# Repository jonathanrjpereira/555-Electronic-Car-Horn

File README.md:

# Electronic Horn | Car / Bike / Bicycle | 555 386 |
The LM555 generates an electronic horn signal which is amplified by an LM386.
The horn can be used on a car, scooter, cycle and motorbike.

**Full Video:**

**Order PCB:**  [PCBWay](https://bit.ly/2VrASCW)

## Electronic Components
| Qty | Component | Buy |
| ------------- | ------------- | ------------- |
| 1 | IC 555 |[AliExpress](http://s.click.aliexpress.com/e/sCv1ACC) |
| 1 | IC LM386 |[AliExpress](http://s.click.aliexpress.com/e/c1pixqXe) |
| 2 | IC Holder |[AliExpress](http://s.click.aliexpress.com/e/cHvnfsrA) |
| 1 | 10Ω 1KΩ 2KΩ Resistor |[AliExpress](http://s.click.aliexpress.com/e/bh4eqrQs) |
| 3 | 10KΩ Potentiometer |[AliExpress](http://s.click.aliexpress.com/e/bN0jkp8y) |
| 1 | Tactile Momentary Push Buttons |[AliExpress](http://s.click.aliexpress.com/e/c77Ajrpq) |
| 1 | 5mm LED |[AliExpress](http://s.click.aliexpress.com/e/wuFpLXS) |
| 1 | 0.1uF 10uF 100uF 220uF Capacitor |[AliExpress](http://s.click.aliexpress.com/e/c9FHzl5W) |
| 1 | 10nF 47nF 0.1uF Capacitor |[AliExpress](http://s.click.aliexpress.com/e/SX7eHuG) |
| 1 | Speaker |[AliExpress](http://s.click.aliexpress.com/e/brMJh46c) |
| 1 | 9V Battery Holder |[AliExpress](http://s.click.aliexpress.com/e/c3jbp72Y) |
| 1 | 9V Battery |[AliExpress](http://s.click.aliexpress.com/e/bbDirGHE) |
| 1 | PCB |[AliExpress](http://s.click.aliexpress.com/e/dhgwzKY) |

| Tools | Buy |
|--|--|
|Soldering Iron|[AliExpress](http://s.click.aliexpress.com/e/E83bSJI) |
|Soldering Wire|[AliExpress](http://s.click.aliexpress.com/e/PdhB0nm) |
|Mini PCB Hand Drill + Bits|[AliExpress](http://s.click.aliexpress.com/e/b93tomjI) |
|Wire Cutter|[AliExpress](http://s.click.aliexpress.com/e/bHFL9vLi) |
|Wire Stripper|[AliExpress](http://s.click.aliexpress.com/e/4yJWedw) |
|Soldering Helping Hands|[AliExpress](http://s.click.aliexpress.com/e/cAQ2StNm) |

## Working
**LM555/NE555:**

The 555 is a highly stable device for generating accurate time delays or oscillation. Additional terminals are provided for triggering or resetting if desired. For stable operation as an oscillator, the free running frequency and duty cycle are accurate controlled with two external resistors and one capacitor. The circuit may be triggered and reset on falling waveforms, and he output circuit can source or sink up to 200mA or drive TTL circuits.

**LM386**

The LM386 is a power amplifier designed for use in low voltage consumer applications. The gain is internally set to 20 to keep external part count low, but the addition of an external resistor and capacitor between pins 1 and 8 will increase the gain to any value from 20 to 200.

The inputs are ground referenced while the output automatically biases to one-half the supply voltage.

**Circuit:**

An LM555 is used to generate the horn signal. The LM555 is connected such that it will trigger itself and free run as an astable multivibrator. The external capacitor charges through Ra+Rb and discharges through Rb. Thus the duty cycle may be precisely set by the ratio of these two resistors.

In this mode of operation, the capacitor charges and discharges between 1/3 VCC and 2/3 VCC. Hence the charge and discharge times, and therefore the frequency are independent of the supply voltage.

The change time (output high) is given by:

And the discharge time (output low) by:

Thus the total period is:

The frequency of oscillation is:

Hence

A momentary switch acts as an input trigger that enables the astable multivibrator to generate a signal of variable frequency.
This signal is then sent to an amplification unit before it is played through a speaker. The frequency and volume of the horn sound can be varied as shown.

A potentiometer R3 (Rb) is varied in order to change the frequency of the signal generated by the LM555. The signal is then passed to the LM386 for amplification.

The input signal is passed through another potentiometer R4 before it reaches the LM386. This pot is used to change the amplitude (volume) of the input signal before amplification.

The LM386 has a 10uF capacitor and 10K potentiometer R5 connected between pins 1 and 8. By varying this pot, we can change the gain of the amplifier and thus the volume of the amplified signal.

A push button/ momentary switch is used to turn on the circuit thereby producing a loud horn sound. Capacitors connected across the supply terminals are used to minimize any noise signals.

## Contributing🛠
Are you an engineer or hobbyist who has a great idea for a new feature in this project? Maybe you have a good idea for a bug fix? Feel free to grab our code & schematics from Github and tinker with it. Don't forget to smash ⭐️ & the Pull Request button.

[![alt text][1.1]][1] [![alt text][2.1]][2] [![alt text][3.1]][3]

[1.1]: https://github.com/jonathanrjpereira/Social-Media-README/blob/master/youtube.png (YouTube)
[2.1]: https://github.com/jonathanrjpereira/Social-Media-README/blob/master/instagram.png (Instagram)
[3.1]: https://github.com/jonathanrjpereira/Social-Media-README/blob/master/github.png (GitHub)

[1]: https://www.youtube.com/channel/UCRW-41O1vy98KKgJRQoYzdg
[2]: https://www.instagram.com/electroguruji/
[3]: https://github.com/jonathanrjpereira

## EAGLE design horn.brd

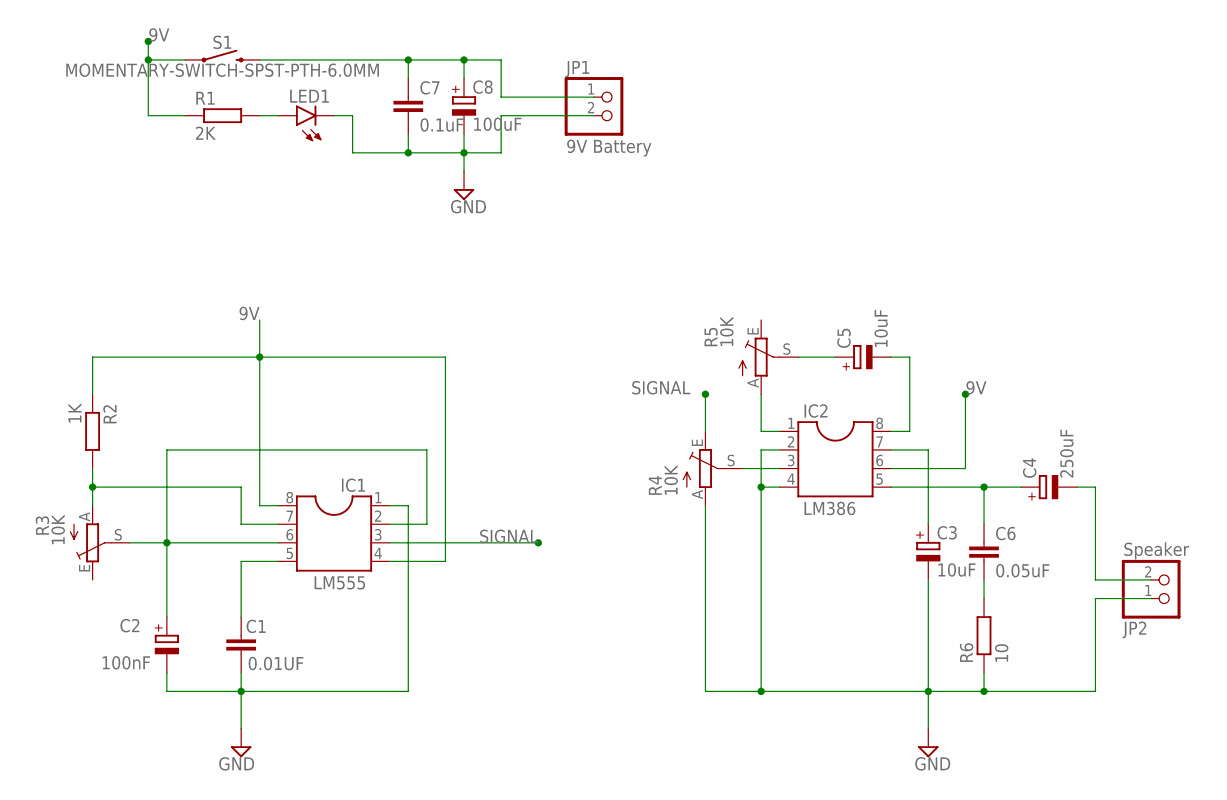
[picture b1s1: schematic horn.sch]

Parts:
C1: 0.01UF; C025-024X044
C2: 100nF; E5-5
C3, C5: 10uF; E5-5
C4: 250uF; E5-5
C6: 0.05uF; C025-024X044
C7: 0.1uF; C025-024X044
C8: 100uF; E5-5
IC1: LM555; SOCKET-08
IC2: LM386; SOCKET-08
JP1: 9V Battery; 1X02
JP2: Speaker; 1X02
LED1: LED5MM
R1: 2K; 0204/5
R2: 1K; 0204/5
R3, R4, R5: 10K; CA6V
R6: 10; 0204/5
S1: MOMENTARY-SWITCH-SPST-PTH-6.0MM; TACTILE_SWITCH_PTH_6.0MM

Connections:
9V: IC1.4, IC1.8, IC2.6, R1.1, R2.1, S1.1
GND: C1.2, C2.-, C3.-, C7.2, C8.-, IC1.1, IC2.2, IC2.4, JP1.2, JP2.1, LED1.K (C), R4.A, R6.1
unnamed: C7.1, C8.+, JP1.1, S1.3 (2)
unnamed: C1.1, IC1.5
unnamed: IC2.3, R4.S
unnamed: LED1.A, R1.2
unnamed: IC1.7, R2.2, R3.A
unnamed: C2.+, IC1.2, IC1.6, R3.S
unnamed: C3.+, IC2.7
unnamed: C4.+, C6.1, IC2.5
unnamed: C6.2, R6.2
unnamed: IC2.1, R5.A
unnamed: C5.+, R5.S
unnamed: C5.-, IC2.8
unnamed: C4.-, JP2.2
SIGNAL: IC1.3, R4.E

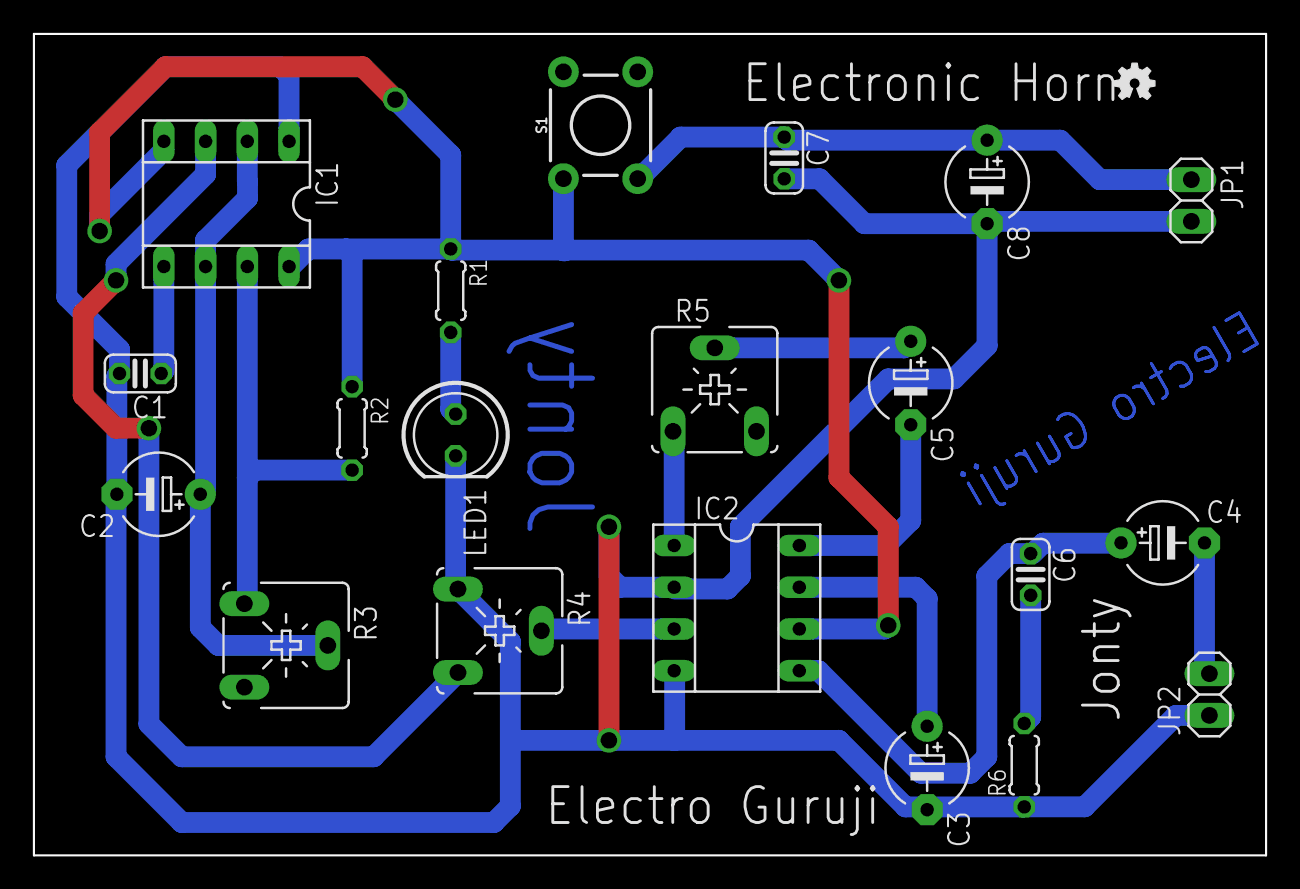
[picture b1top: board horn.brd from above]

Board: 2 copper layers, 75.0 x 50.0 mm, 21 parts (0 on the bottom side), 16 nets.

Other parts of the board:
U$1: OSHW-LOGO-MINI

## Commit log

2019-03-12 schematic
2019-03-12 board
2019-03-13 All layers
2019-03-13 Logos
2019-03-13 LM386
2019-03-13 Working + BD
2019-03-13 Parts List
2019-05-15 Gerber files
2019-05-15 PCB Order Link
2019-05-30 BOM CSV

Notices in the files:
parts and their libraries:
SparkFun-Switches: Licensing: Creative Commons ShareAlike 4.0 International - https://creativecommons.org/licenses/by-sa/4.0
